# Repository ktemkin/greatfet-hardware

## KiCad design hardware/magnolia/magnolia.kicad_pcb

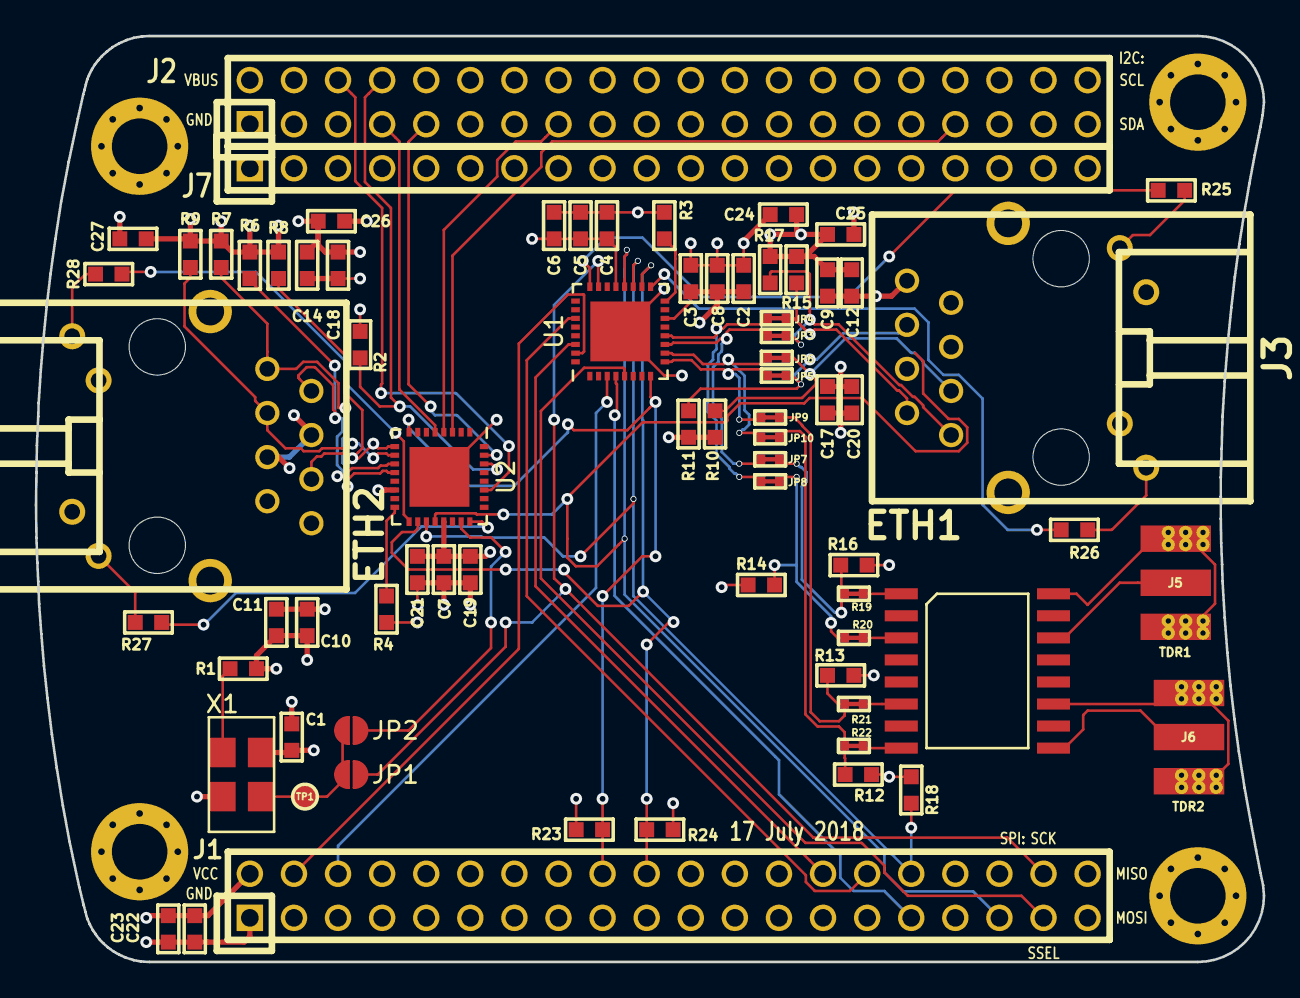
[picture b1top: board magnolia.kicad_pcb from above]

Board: 4 copper layers, 70.7 x 53.3 mm, 77 parts (0 on the bottom side), 56 nets.

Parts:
C1, C2, C4, C7: 10nF; 0603
C3, C6, C10, C24, C25, C26, C27: 100nF; 0603
C5, C8, C9, C11, C17, C18, C19: 1uF; 0603
C12, C14, C20, C21: 0.1uF; 0603
C22, C23: CP; 0603
J1: NEIGHBOR1; HEADER-2x20
J2: NEIGHBOR2; HEADER-2x20
J3: ETH1; rj45-wiznet-rb1-125bag1a
J4: ETH2; rj45-wiznet-rb1-125bag1a
J5: TDR1; SMA-EDGE
J6: TDR2; SMA-EDGE
J7: BONUS_ROW; HEADER-1x20
JP1, JP2: Jumper; JUMPER-SOLDER-SMD
JP3, JP4, JP5, JP6, JP7, JP8, JP9, JP10: Jumper_NC_Small; 0402-SHORT-10MIL
MH1, MH2, MH3, MH4: MOUNTING_HOLE; HOLE126MIL-COPPER
R1, R23, R24: 10K; 0603
R2: 2K49; 0603
R3, R4: 4K87 +/- 1%; 0603
R6, R7, R8, R9, R10, R11, R15, R17: 49R9; 0603
R12, R13, R14, R16: 0R; 0603
R18: 2K2; 0603
R19, R20, R21, R22: R-SHORTED; 0402-SHORT-10MIL
R25, R26, R27, R28: 1K; 0603
T1: 749010012A
TP1: Test_Point; TESTPOINT-50MIL
U1, U2: DP83822; QFN-32_EP_5.15x5.15_Pitch0.5mm
X1: ASFL1

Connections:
+3V3: C1.1, C2.1, C3.1, C4.1, C5.1, C6.1, C7.1, C8.1, C9.1, C10.1, C11.1, C12.1, C14.1, C17.1, C18.1, C19.1, C20.1, C21.1, C22.1, C23.1, C24.2, C25.2, C26.2, C27.2, J1.2, J3.4, J3.5, J4.4, J4.5, J7.20, R1.1, R2.1, R6.1, R7.1, R8.1, R9.1, R10.1, R11.1, R12.1, R13.1, R14.1, R15.1, R16.1, R17.1, R18.1, R23.1, R24.1, U1.14, U1.21, U2.14, U2.21, X1.4
/ENET1_RD_N: J3.6, JP5.2, R11.2
/ENET1_RD_P: J3.3, JP6.2, R10.2
/ENET1_RMII_CLK: J1.38, JP1.2, U1.23
/ENET1_TD_N: J3.1, JP3.2, R17.2
/ENET1_TD_P: J3.2, JP4.2, R15.2
/ENET2_RD_N: J4.6, R8.2, U2.9
/ENET2_RD_P: J4.3, R9.2, U2.10
/ENET2_RMII_CLK: JP2.2, U2.23
/ENET2_TD_N: J4.2, R6.2, U2.11
/ENET2_TD_P: J4.1, R7.2, U2.12
/INT_PWDN: J1.18, R23.2, U1.8, U2.8
/MII_CRS_DV: J1.30, U1.27
/MII_RX_D0: J1.28, U1.30
/MII_RX_D1: J1.4, U1.31
/MII_TX_D0: J1.31, U1.4
/MII_TX_D1: J1.37, U1.5
/MII_TX_EN: J1.6, U1.3
/PHY1_RD_N: JP5.1, JP9.1, U1.9
/PHY1_RD_P: JP6.1, JP10.1, U1.10
/PHY1_TD_N: JP3.1, JP7.1, U1.11
/PHY1_TD_P: JP4.1, JP8.1, U1.12
/PHY_RESET: J1.20, R24.2, U1.18, U2.18
/REF_CLK_ENABLE: R1.2, X1.1
/SGPIO_CRS_DV: J2.6, U2.27
/SGPIO_RX_D0: J2.8, R2.2, U2.30
/SGPIO_RX_D1: J2.9, U2.31
/SGPIO_TX_D0: J2.15, U2.4
/SGPIO_TX_D1: J2.7, U2.5
/SGPIO_TX_EN: J2.33, U2.3
/SMI_MDC: J1.35, U1.20, U2.20
/SMI_MDIO: J1.32, R18.2, U1.19, U2.19
/TDR1_RD_N: JP9.2, R13.2, R21.2
/TDR1_RD_P: JP10.2, R12.2, R22.2
/TDR1_SMA_RX_N: J6.2, T1.11
/TDR1_SMA_RX_P: J6.1, T1.9
/TDR1_SMA_TD_N: J5.2, T1.16
/TDR1_SMA_TD_P: J5.1, T1.14
/TDR1_TD_N: JP7.2, R16.2, R19.2
/TDR1_TD_P: JP8.2, R14.2, R20.2
/TDR1_XFMR_RD_N: R21.1, T1.6
/TDR1_XFMR_RD_P: R22.1, T1.8
/TDR1_XFMR_TD_N: R19.1, T1.1
/TDR1_XFMR_TD_P: R20.1, T1.3
GND: C1.2, C2.2, C3.2, C4.2, C5.2, C6.2, C7.2, C8.2, C9.2, C10.2, C11.2, C12.2, C14.2, C17.2, C18.2, C19.2, C20.2, C21.2, C22.2, C23.2, C24.1, C25.1, C26.1, C27.1, J1.1, J2.1, J3.8, J3.10, J3.11, J3.13, J4.8, J4.10, J4.11, J4.13, J7.1, J7.10, J7.19, MH1.1, MH2.1, MH3.1, MH4.1, R3.1, R4.1, U1.PAD, U2.PAD, X1.2
unnamed: J3.9, R25.1
unnamed: J3.12, R26.1
unnamed: J4.9, R27.1
unnamed: J4.12, R28.1
unnamed: JP1.1, JP2.1, TP1.1, X1.3
unnamed: R3.2, U1.16
unnamed: R4.2, U2.16
unnamed: R25.2, U1.24
unnamed: R26.2, U1.17
unnamed: R27.2, U2.24
unnamed: R28.2, U2.17

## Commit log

2018-01-10 Add schematic for Indigo glitching board.
2018-01-10 Switch to the GlitchKit version of the GSG symbols.
2018-07-03 add KiCad-targeted gitignore
2018-07-03 magnolia: import WIP ethernet / TDR board
2018-07-10 magnolia: route more of Magnolia
2018-07-16 magnolia: route more
2018-09-04 magnolia: check in completed (but never cheked in) r0 PCB
